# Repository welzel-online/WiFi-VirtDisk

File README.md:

## WiFi-VirtDisk ##

The WiFi-VirtDisk is a network-based storage solution that replaces or supplements the classic SD card approach. The hardware consists of an ESP8266 (D1 mini), which is connected to the SPI port (SD card).

Unlike SD card support, the WiFi-VirtDisk relies on its own SPI protocol, which is fully implemented in the ESP8266. This communicates directly with the IOS of the Z80-MBC2, which I have also adapted. There, the user can flexibly choose whether they want to work with a local SD card or via the WiFi-VirtDisk.
The ESP8266 then communicates via WLAN to a server programme that runs on both Windows 10/11 and Linux.

Technical overview:
- Own SPI protocol instead of SD emulation
- Switchable in the IOS between SD card and WiFi-VirtDisk
- WLAN connection via ESP8266 to a self-developed server programme
- Virtual disk images are stored centrally on the server and appear in the CP/M system like classic drives
- A virtual disk image is generated from a directory on the server.
- Extensibility: the proprietary protocol leaves room for future features

https://www.welzel-online.ch

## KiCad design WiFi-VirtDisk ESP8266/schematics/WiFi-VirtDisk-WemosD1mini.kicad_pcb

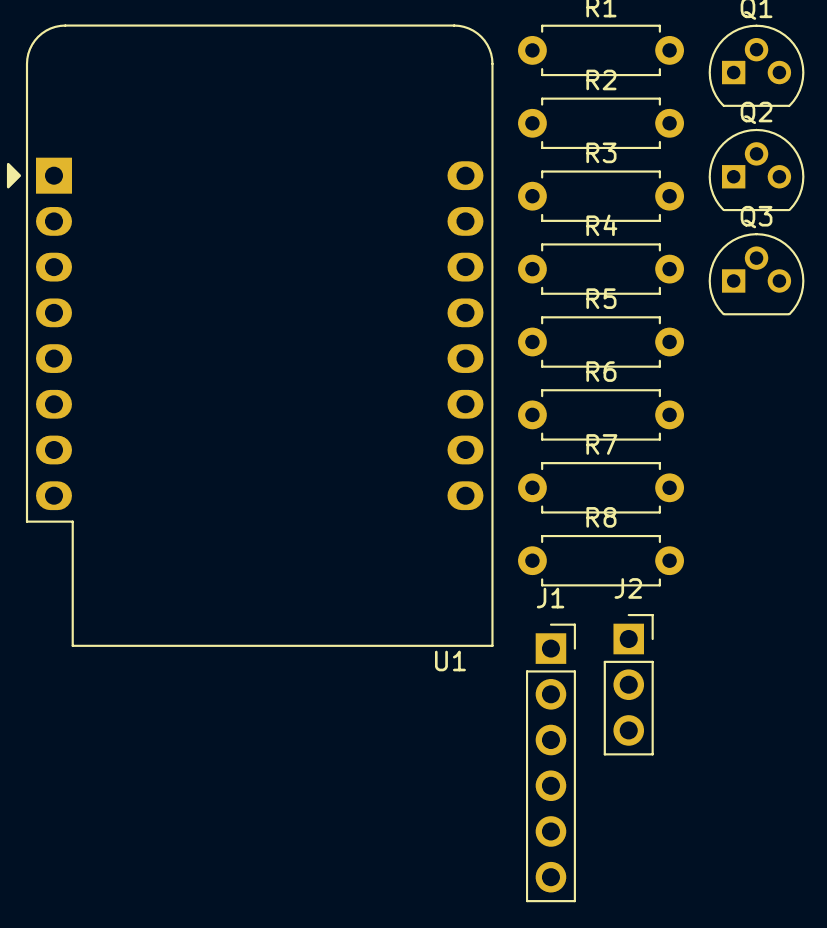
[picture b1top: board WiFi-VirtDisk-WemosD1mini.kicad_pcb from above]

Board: 2 copper layers, 14 parts (0 on the bottom side), 17 nets, no tracks yet.

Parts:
J1: SD_MOD; PinSocket_1x06_P2.54mm_Vertical
J2: Z80_MOD; PinSocket_1x03_P2.54mm_Vertical
Q1: 2N2907A; TO-92
Q2, Q3: 2N2222A; TO-92
R1: 1k; R_Axial_DIN0207_L6.3mm_D2.5mm_P7.62mm_Horizontal
R2, R5, R6: 10k; R_Axial_DIN0207_L6.3mm_D2.5mm_P7.62mm_Horizontal
R3, R7: 2k2; R_Axial_DIN0207_L6.3mm_D2.5mm_P7.62mm_Horizontal
R4, R8: 3k3; R_Axial_DIN0207_L6.3mm_D2.5mm_P7.62mm_Horizontal
U1: WeMos_D1_mini; WEMOS_D1_mini_light

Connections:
/SS_EN: R1.1, U1.14 (SCL/D1)
GND: J1.1, J2.2, Q1.3 (C), Q2.1 (E), Q3.1 (E), R4.1, R8.1, U1.10 (GND)
MISO: J1.3, U1.5 (MISO/D6)
MOSI: J1.4, R3.1
unnamed: Q1.2 (B), R2.1
unnamed: Q1.1 (E), R1.2
unnamed: Q2.2 (B), R5.2
unnamed: Q3.2 (B), R6.2
unnamed: R5.1, U1.12 (D3)
unnamed: R6.1, U1.11 (D4)
unnamed: R3.2, R4.2, U1.6 (MOSI/D7)
unnamed: R7.1, R8.2, U1.4 (SCK/D5)
SCK: J1.5, R7.2
VCC: J1.2, U1.9 (5V)
Z80_RST: J2.1, Q2.3 (C)
Z80_USR: J2.3, Q3.3 (C)
/CS: J1.6, R2.2

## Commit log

2025-09-21 - First import of the WiFi-VirtDisk: * IOS for Z80-MBC2 * Schematic for ESP8266 * Client firmware for ESP8266 * Server software for PC (Windows/Linux)
2025-09-22 - Added first version of the manual (quick guide).
2025-09-23 - Added different version.in files to represent the differences from svn and git. - Bumped the minimal version of cmake to 3.10. - Minor updates to the manual.
2025-09-23 - Bug fix: Corrected the version number in the version-git.in.
2025-10-24 - Updated the manuals.
2025-10-24 - Moved the manuals to the doc directory.
2025-10-25 - The address of the autoboot.bin file can now be entered as decimal or hexadecimal number.
2025-10-25 - Bug fix: Additional WiFiManager parameters must be saved by the user. - Code cleanup.
2025-10-25 - WiFi-VirtDisk-Server can now emulate up to 4 disk drives.
2025-11-16 - Added documentation of the used protocols.
2025-11-16 - Improved the error handling, if the WiFi-VirtDisk-Client (ESP8266) is not connected to the WiFi or the Server. - Bumped the version of the WiFi-VirtDisk-Client to v1.0.0. - Little tweaks of the ser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
